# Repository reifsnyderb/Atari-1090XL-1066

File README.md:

# 1066

64k/256k 1090XL DRAM Card

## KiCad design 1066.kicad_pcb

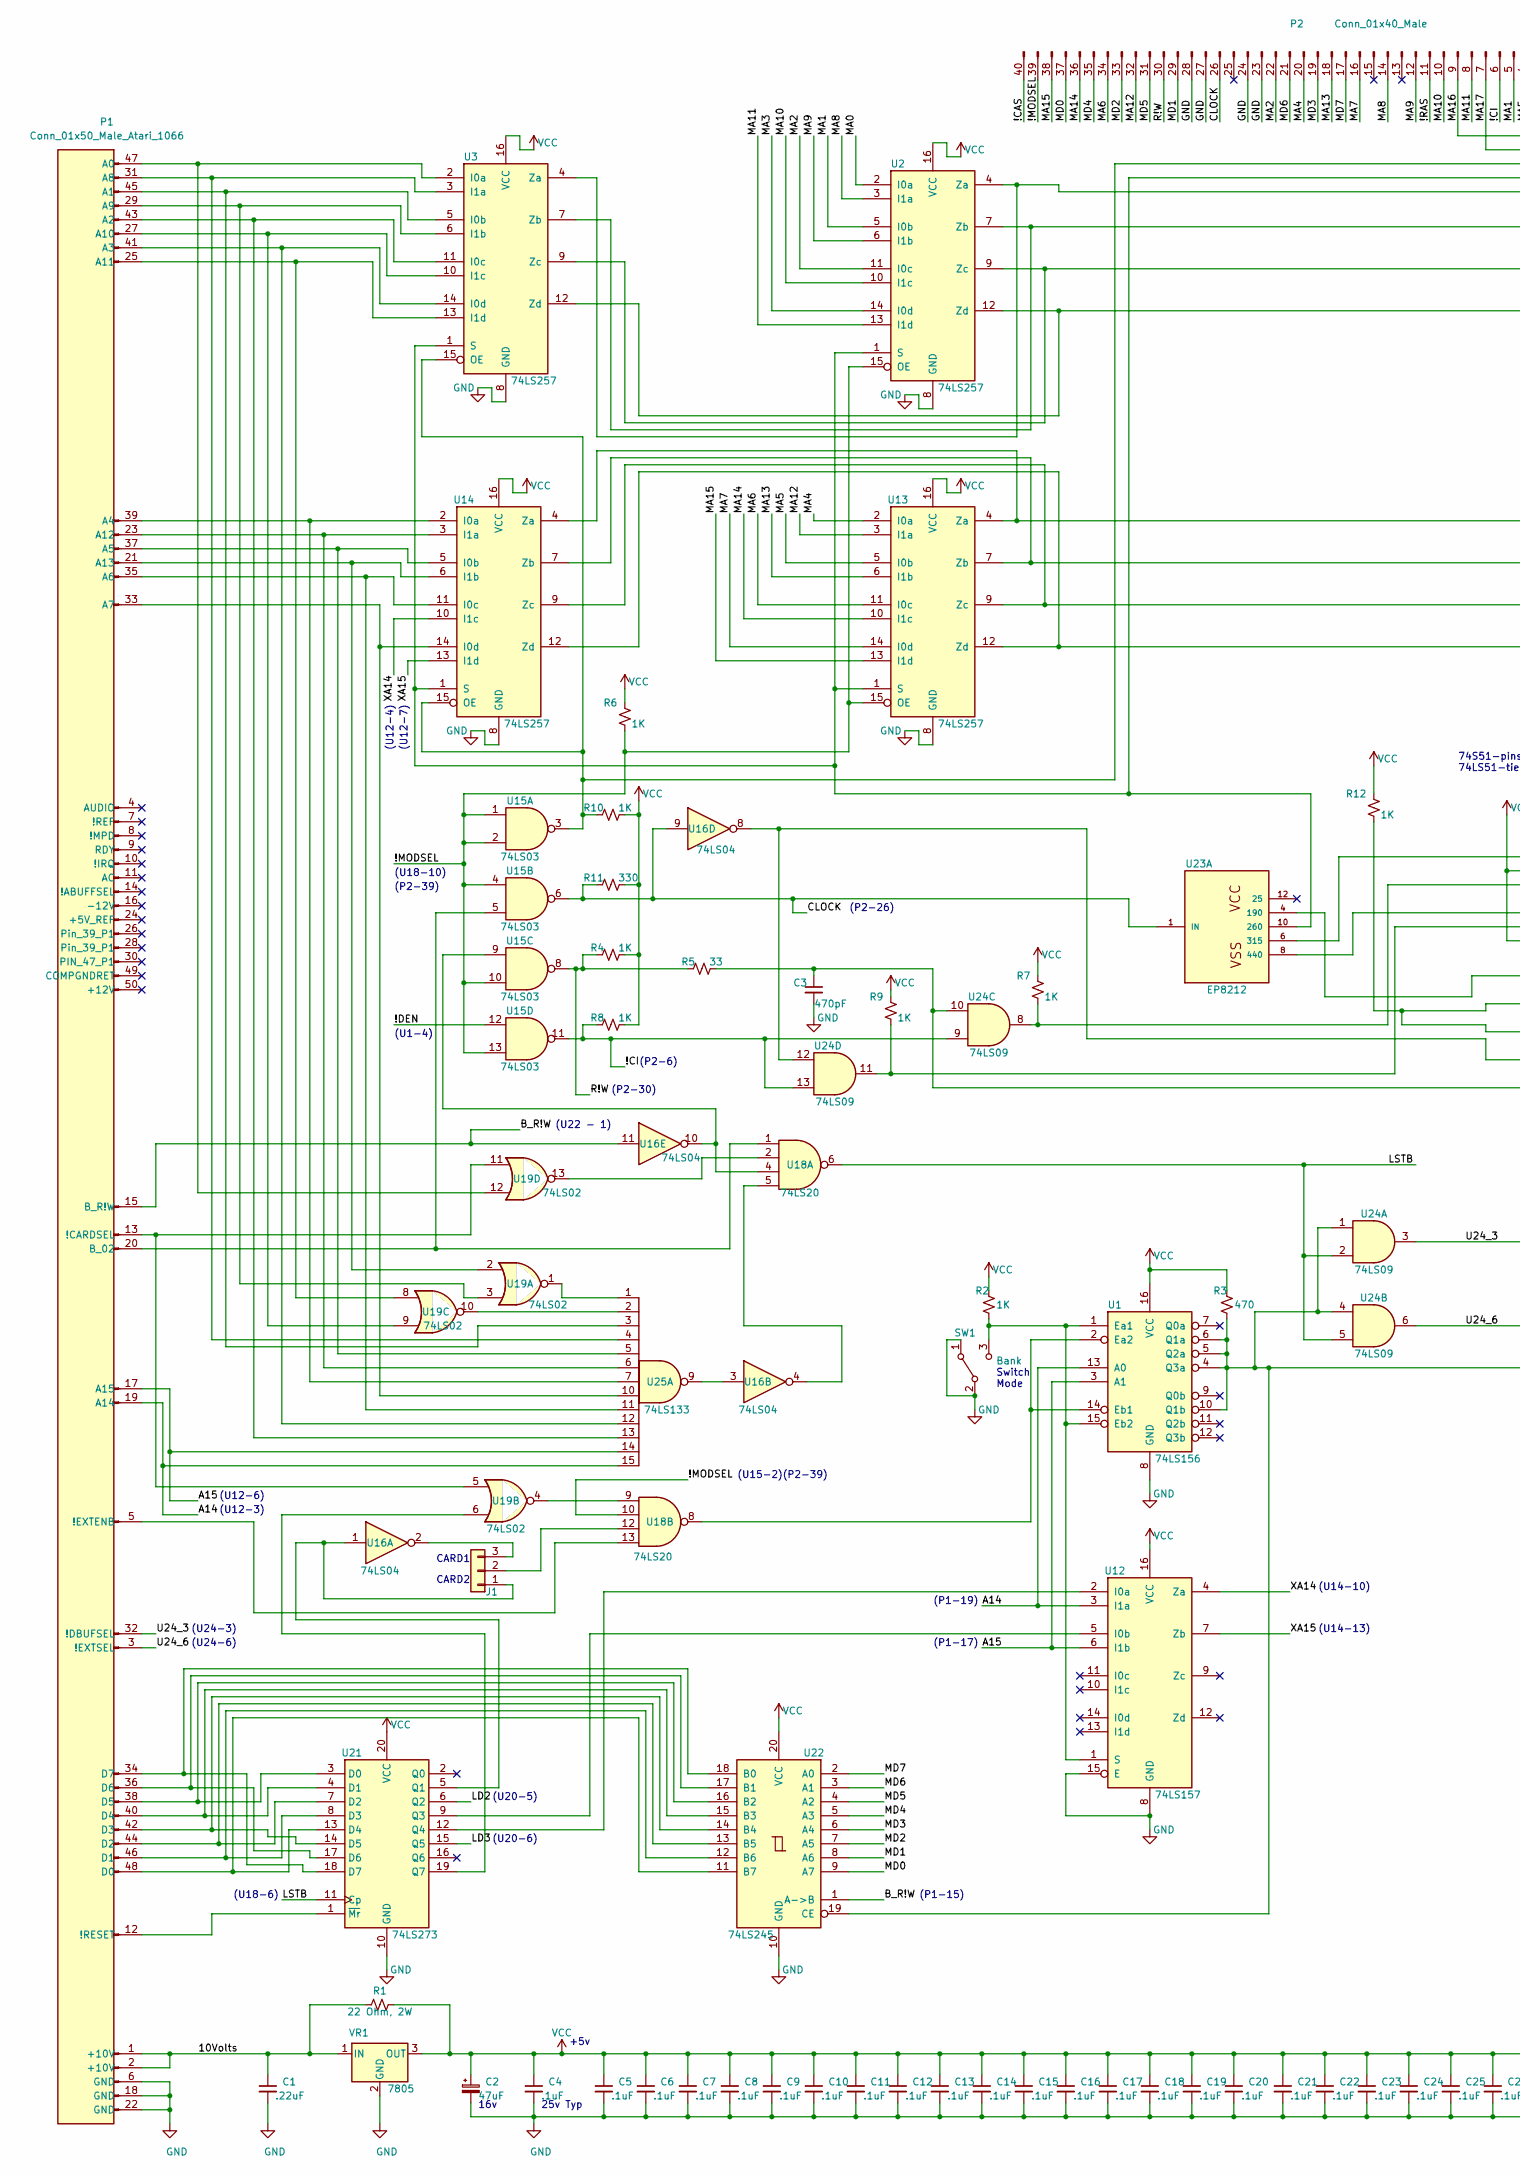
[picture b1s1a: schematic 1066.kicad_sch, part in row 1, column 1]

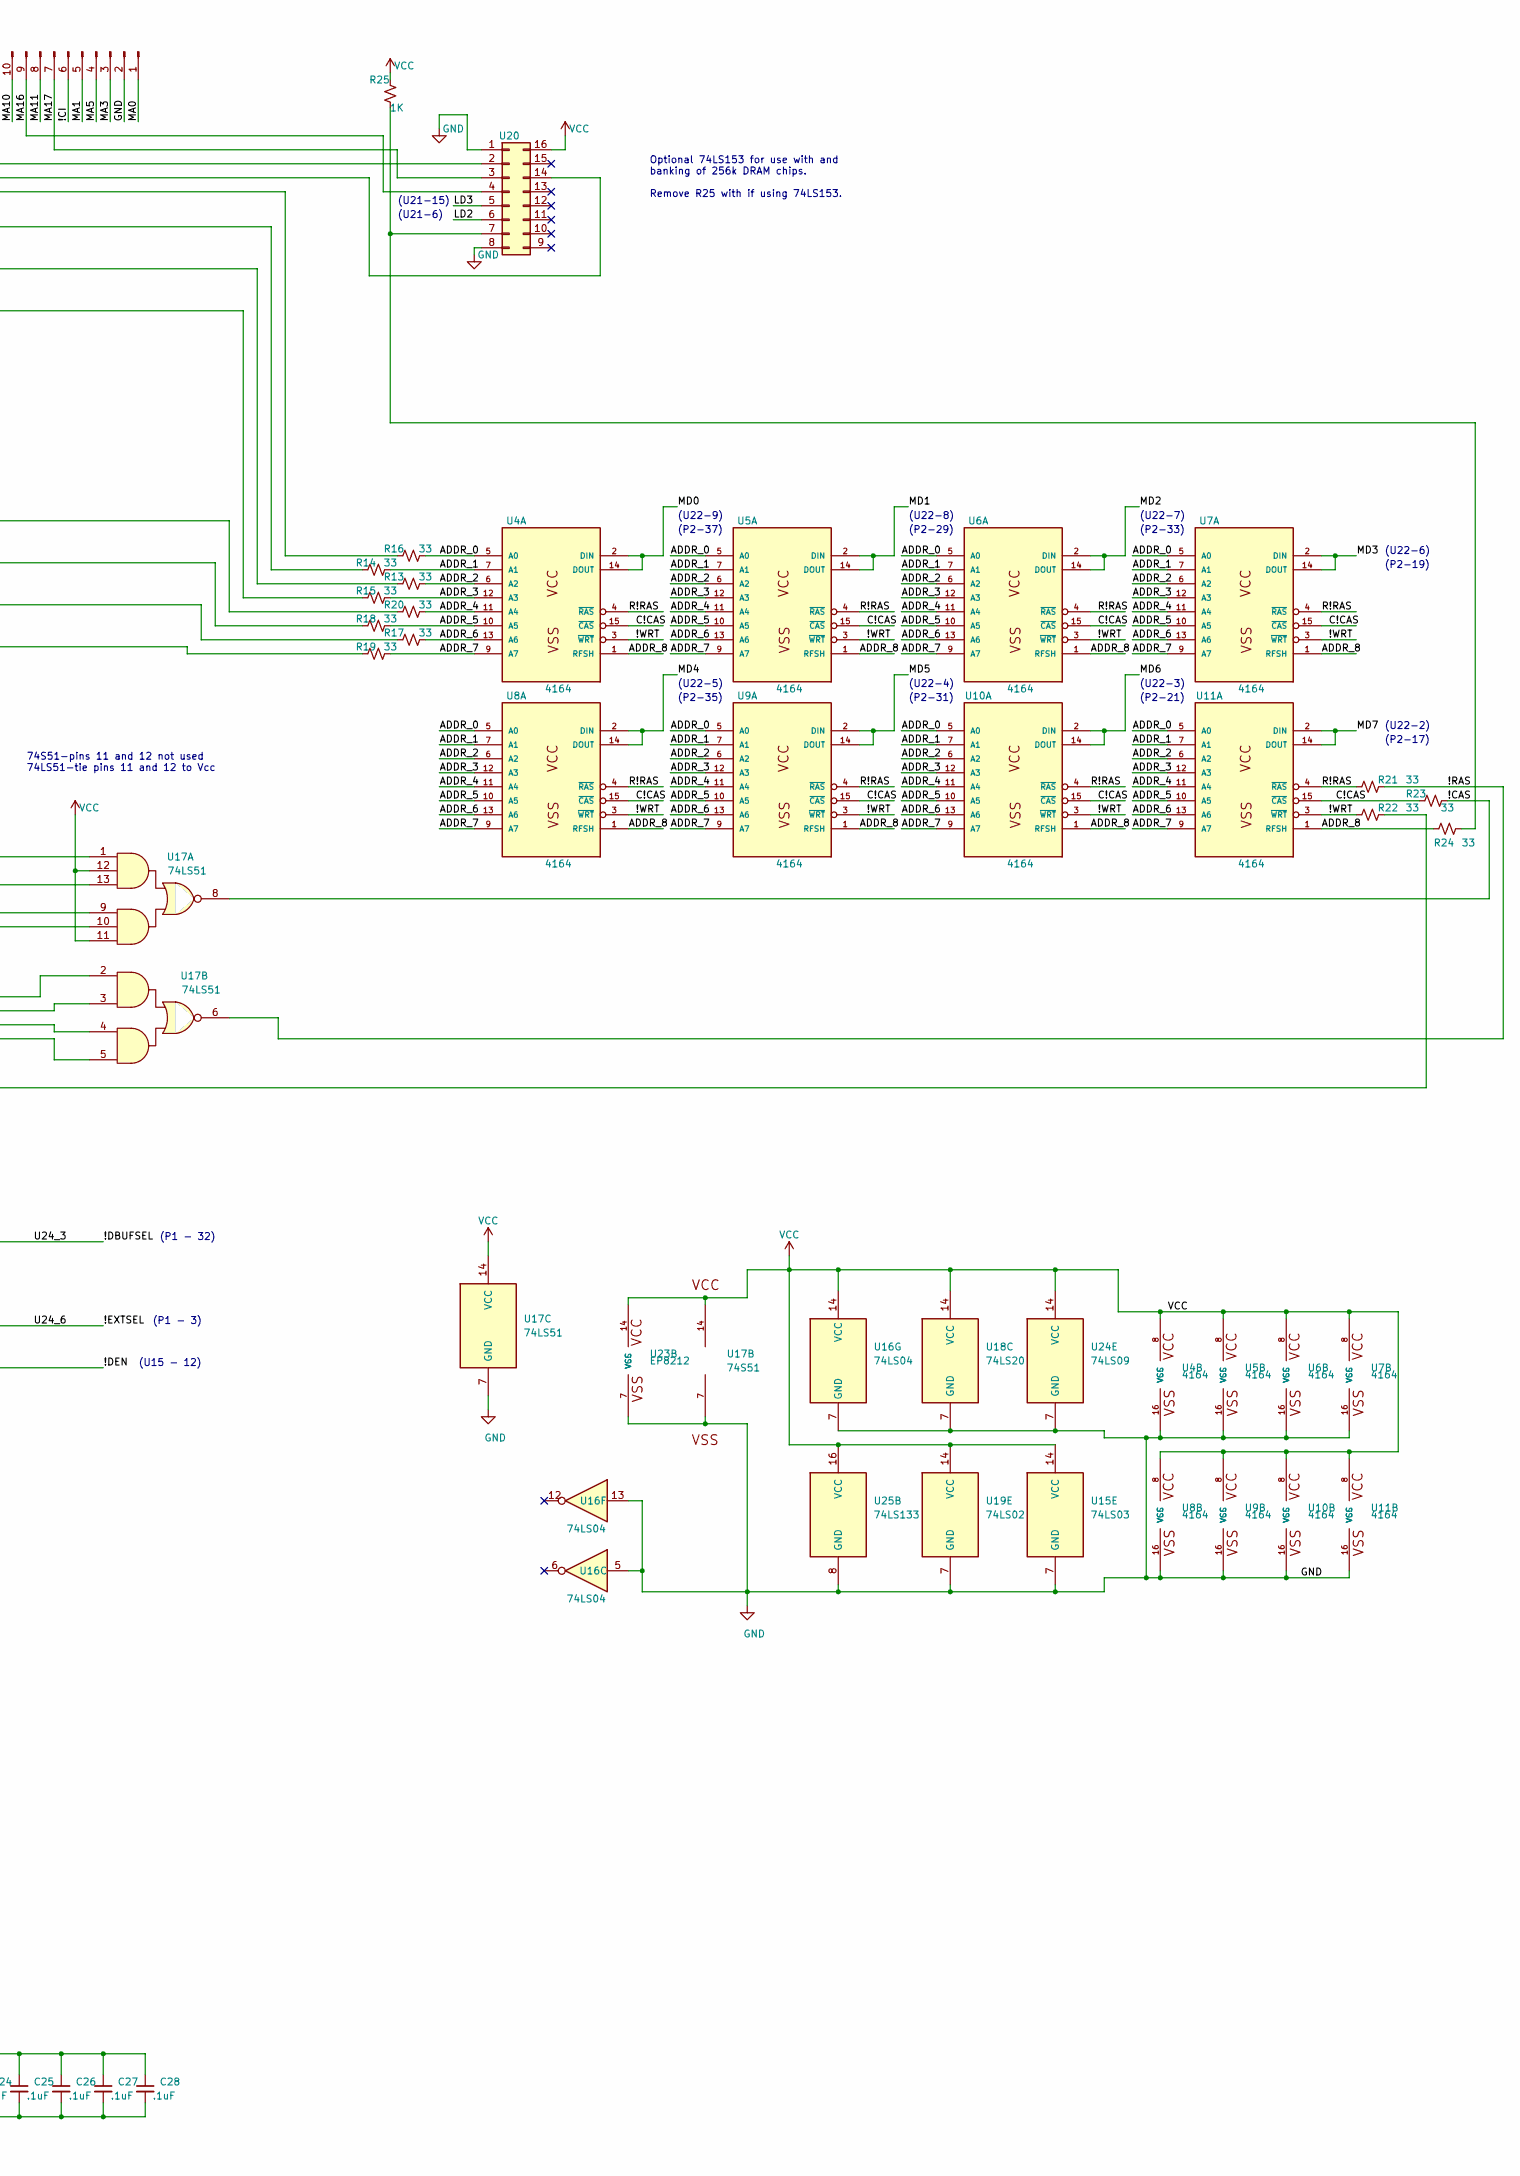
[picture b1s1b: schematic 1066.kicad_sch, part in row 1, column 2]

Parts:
C1: .22uF; C_Axial_L3.8mm_D2.6mm_P7.50mm_Horizontal
C2: 47uF; CP_Axial_L21.0mm_D8.0mm_P28.00mm_Horizontal
C3: 470pF; C_Rect_L24.0mm_W8.3mm_P22.50mm_MKT
C4, C5, C6, C7, C8, C9, C10, C11, C12, C13, C14, C15, C16, C17, C18, C19, C20, C21, C22, C23, C24, C25, C26, C27, C28: .1uF; C_Axial_L3.8mm_D2.6mm_P7.50mm_Horizontal
J1: Conn_01x03; PinHeader_1x03_P2.54mm_Vertical
P1: Conn_01x50_Male_Atari_1066; PARALLEL_BUS_INTERFACE_DEVICE
P2: Conn_01x40_Male; PinHeader_2x20_P2.54mm_Vertical
R1: 22 Ohm, 2W; R_Axial_DIN0516_L15.5mm_D5.0mm_P30.48mm_Horizontal
R2, R4, R6, R7, R8, R9, R10, R12, R25: 1K; R_Axial_DIN0207_L6.3mm_D2.5mm_P10.16mm_Horizontal
R3: 470; R_Axial_DIN0207_L6.3mm_D2.5mm_P10.16mm_Horizontal
R5, R13, R14, R15, R16, R17, R18, R19, R20, R21, R22, R23, R24: 33; R_Axial_DIN0207_L6.3mm_D2.5mm_P10.16mm_Horizontal
R11: 330; R_Axial_DIN0207_L6.3mm_D2.5mm_P10.16mm_Horizontal
SW1: Bank; SPDT_Switch
U1: 74LS156; DIP-16_W7.62mm_Socket
U2, U3, U13, U14: 74LS257; DIP-16_W7.62mm
U4, U5, U6, U7, U8, U9, U10, U11: 4164; DIP-16_W7.62mm
U12: 74LS157; DIP-16_W7.62mm
U15: 74LS03; DIP-14_W7.62mm
U16: 74LS04; DIP-14_W7.62mm
U17: 74S51; DIP-14_W7.62mm_Socket
U18: 74LS20; DIP-14_W7.62mm
U19: 74LS02; DIP-14_W7.62mm
U20: Conn_02x08_Counter_Clockwise; DIP-16_W7.62mm
U21: 74LS273; DIP-20_W7.62mm
U22: 74LS245; DIP-20_W7.62mm
U23: EP8212; DIP-14_W7.62mm
U24: 74LS09; DIP-14_W7.62mm
U25: 74LS133; DIP-16_W7.62mm
VR1: 7805; TO-220-3_Horizontal_TabDown

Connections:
/10Volts: C1.1, P1.1 (+10V), P1.2 (+10V), R1.2, VR1.1 (IN)
/!CAS: P2.40, R23.1, U17.8
/!CI: P2.6, R8.2, U15.11, U24.9, U24.13
/!DBUFSEL: P1.32 (!DBUFSEL), U24.3
/!DEN: R3.2, U1.4 (Q3a), U1.5 (Q2a), U1.6 (Q1a), U1.10 (Q1b), U15.12, U22.19 (CE), U24.1, U24.4
/!EXTSEL: P1.3 (!EXTSEL), U24.6
/!MODSEL: P2.39, R6.1, U2.15 (OE), U13.15 (OE), U15.1, U15.2, U15.4, U15.10, U15.13, U18.10
/!RAS: P2.11, R21.1, U17.6
/!WRT: R22.2, U4.3 (~WRT), U5.3 (~WRT), U6.3 (~WRT), U7.3 (~WRT), U8.3 (~WRT), U9.3 (~WRT), U10.3 (~WRT), U11.3 (~WRT)
/A14: P1.19 (A14), U1.13 (A0), U12.3 (I1a), U25.15
/A15: P1.17 (A15), U1.3 (A1), U12.6 (I1b), U25.14
/ADDR_0: R16.1, U4.5 (A0), U5.5 (A0), U6.5 (A0), U7.5 (A0), U8.5 (A0), U9.5 (A0), U10.5 (A0), U11.5 (A0)
/ADDR_1: R14.1, U4.7 (A1), U5.7 (A1), U6.7 (A1), U7.7 (A1), U8.7 (A1), U9.7 (A1), U10.7 (A1), U11.7 (A1)
/ADDR_2: R13.1, U4.6 (A2), U5.6 (A2), U6.6 (A2), U7.6 (A2), U8.6 (A2), U9.6 (A2), U10.6 (A2), U11.6 (A2)
/ADDR_3: R15.1, U4.12 (A3), U5.12 (A3), U6.12 (A3), U7.12 (A3), U8.12 (A3), U9.12 (A3), U10.12 (A3), U11.12 (A3)
/ADDR_4: R20.1, U4.11 (A4), U5.11 (A4), U6.11 (A4), U7.11 (A4), U8.11 (A4), U9.11 (A4), U10.11 (A4), U11.11 (A4)
/ADDR_5: R18.1, U4.10 (A5), U5.10 (A5), U6.10 (A5), U7.10 (A5), U8.10 (A5), U9.10 (A5), U10.10 (A5), U11.10 (A5)
/ADDR_6: R17.1, U4.13 (A6), U5.13 (A6), U6.13 (A6), U7.13 (A6), U8.13 (A6), U9.13 (A6), U10.13 (A6), U11.13 (A6)
/ADDR_7: R19.1, U4.9 (A7), U5.9 (A7), U6.9 (A7), U7.9 (A7), U8.9 (A7), U9.9 (A7), U10.9 (A7), U11.9 (A7)
/ADDR_8: R24.2, U4.1 (RFSH), U5.1 (RFSH), U6.1 (RFSH), U7.1 (RFSH), U8.1 (RFSH), U9.1 (RFSH), U10.1 (RFSH), U11.1 (RFSH)
/B_R!W: P1.15 (B_R!W), U16.11, U22.1 (A->B)
/C!CAS: R23.2, U4.15 (~CAS), U5.15 (~CAS), U6.15 (~CAS), U7.15 (~CAS), U8.15 (~CAS), U9.15 (~CAS), U10.15 (~CAS), U11.15 (~CAS)
/CLOCK: P2.26, R11.2, U15.6, U16.9, U23.1 (IN)
/LD2: U20.6, U21.6 (Q2)
/LD3: U20.5, U21.15 (Q5)
/LSTB: U18.6, U21.11 (Cp), U24.2, U24.5
/MA0: P2.1, U2.2 (I0a)
/MA1: P2.5, U2.5 (I0b)
/MA2: P2.22, U2.11 (I0c)
/MA3: P2.3, U2.14 (I0d)
/MA4: P2.20, U13.2 (I0a)
/MA5: P2.4, U13.5 (I0b)
/MA6: P2.34, U13.11 (I0c)
/MA7: P2.16, U13.14 (I0d)
/MA8: P2.14, U2.3 (I1a)
/MA9: P2.12, U2.6 (I1b)
/MA10: P2.10, U2.10 (I1c)
/MA11: P2.8, U2.13 (I1d)
/MA12: P2.32, U13.3 (I1a)
/MA13: P2.18, U13.6 (I1b)
/MA14: P2.36, U13.10 (I1c)
/MA15: P2.38, U13.13 (I1d)
/MA16: P2.9, U20.4
/MA17: P2.7, U20.3
/MD0: P2.37, U4.2 (DIN), U4.14 (DOUT), U22.9 (A7)
/MD1: P2.29, U5.2 (DIN), U5.14 (DOUT), U22.8 (A6)
/MD2: P2.33, U6.2 (DIN), U6.14 (DOUT), U22.7 (A5)
/MD3: P2.19, U7.2 (DIN), U7.14 (DOUT), U22.6 (A4)
/MD4: P2.35, U8.2 (DIN), U8.14 (DOUT), U22.5 (A3)
/MD5: P2.31, U9.2 (DIN), U9.14 (DOUT), U22.4 (A2)
/MD6: P2.21, U10.2 (DIN), U10.14 (DOUT), U22.3 (A1)
/MD7: P2.17, U11.2 (DIN), U11.14 (DOUT), U22.2 (A0)
/R!RAS: R21.2, U4.4 (~RAS), U5.4 (~RAS), U6.4 (~RAS), U7.4 (~RAS), U8.4 (~RAS), U9.4 (~RAS), U10.4 (~RAS), U11.4 (~RAS)
/R!W: P2.30, R4.2, R5.2, U15.8
/XA14: U12.4 (Za), U14.10 (I1c)
/XA15: U12.7 (Zb), U14.13 (I1d)
GND: C1.2, C2.2, C3.2, C4.2, C5.2, C6.2, C7.2, C8.2, C9.2, C10.2, C11.2, C12.2, C13.2, C14.2, C15.2, C16.2, C17.2, C18.2, C19.2, C20.2, C21.2, C22.2, C23.2, C24.2, C25.2, C26.2, C27.2, C28.2, P1.6 (GND), P1.18 (GND), P1.22 (GND), P2.2, P2.23, P2.24, P2.27, P2.28, SW1.1 (A), SW1.2 (B), U1.8 (GND), U2.8 (GND), U3.8 (GND), U4.16 (VSS), U5.16 (VSS), U6.16 (VSS), U7.16 (VSS), U8.16 (VSS), U9.16 (VSS), U10.16 (VSS), U11.16 (VSS), U12.8 (GND), U12.15 (E), U13.8 (GND), U14.8 (GND), U15.7 (GND), U16.5, U16.7 (GND), U16.13, U17.7 (GND), U18.7 (GND), U19.7 (GND), U20.1, U20.8, U21.10 (GND), U22.10 (GND), U23.7 (VSS), U24.7 (GND), U25.8 (GND), VR1.2 (GND)
unnamed: C3.1, R5.1, R22.1, U24.10
unnamed: J1.1, U16.1, U21.5 (Q1)
unnamed: J1.2, U18.12
unnamed: J1.3, U16.2
unnamed: P1.5 (!EXTENB), U18.13
unnamed: P1.12 (!RESET), U21.1 (~Mr)
unnamed: P1.13 (!CARDSEL), U19.5, U19.11
unnamed: P1.20 (B_02), U15.5, U18.1
unnamed: P1.21 (A13), U14.6 (I1b), U19.2
unnamed: P1.23 (A12), U14.3 (I1a), U25.6
unnamed: P1.25 (A11), U3.13 (I1d), U19.8
unnamed: P1.27 (A10), U3.10 (I1c), U19.9
unnamed: P1.29 (A9), U3.6 (I1b), U19.3
unnamed: P1.31 (A8), U3.3 (I1a), U25.4
unnamed: P1.33 (A7), U14.14 (I0d), U25.10
unnamed: P1.34 (D7), U21.18 (D7), U22.18 (B0)
unnamed: P1.35 (A6), U14.11 (I0c), U25.11
unnamed: P1.36 (D6), U21.17 (D6), U22.17 (B1)
unnamed: P1.37 (A5), U14.5 (I0b), U25.5
unnamed: P1.38 (D5), U21.3 (D0), U22.16 (B2)
unnamed: P1.39 (A4), U14.2 (I0a), U25.7
unnamed: P1.40 (D4), U21.4 (D1), U22.15 (B3)
unnamed: P1.41 (A3), U3.14 (I0d), U25.12
unnamed: P1.42 (D3), U21.14 (D5), U22.14 (B4)
unnamed: P1.43 (A2), U3.11 (I0c), U25.13
unnamed: P1.44 (D2), U21.7 (D2), U22.13 (B5)
unnamed: P1.45 (A1), U3.5 (I0b), U25.3
unnamed: P1.46 (D1), U21.8 (D3), U22.12 (B6)
unnamed: P1.47 (A0), U3.2 (I0a), U19.12
unnamed: P1.48 (D0), U21.13 (D4), U22.11 (B7)
unnamed: R2.2, SW1.3 (C), U1.1 (Ea1), U1.15 (Eb2), U12.1 (S)
unnamed: R7.1, U17.13, U24.8
unnamed: R9.1, U17.10, U24.11
unnamed: R10.2, U3.15 (OE), U14.15 (OE), U15.3, U20.2
unnamed: R12.1, U17.3, U17.4
unnamed: R13.2, U2.9 (Zc), U3.9 (Zc)
unnamed: R14.2, U2.7 (Zb), U3.7 (Zb)
unnamed: R15.2, U2.12 (Zd), U3.12 (Zd)
unnamed: R16.2, U2.4 (Za), U3.4 (Za)
unnamed: R17.2, U13.9 (Zc), U14.9 (Zc)
unnamed: R18.2, U13.7 (Zb), U14.7 (Zb)
unnamed: R19.2, U13.12 (Zd), U14.12 (Zd)
unnamed: R20.2, U13.4 (Za), U14.4 (Za)
unnamed: R24.1, R25.1, U20.7
unnamed: U1.2 (Ea2), U1.14 (Eb1), U18.8
unnamed: U12.2 (I0a), U21.12 (Q4)
unnamed: U12.5 (I0b), U21.9 (Q3)
unnamed: U2.1 (S), U3.1 (S), U13.1 (S), U14.1 (S), U20.14, U23.10 (260)
unnamed: U15.9, U16.10, U18.4
unnamed: U16.3, U25.9
unnamed: U16.4, U18.5
unnamed: U16.8, U17.5, U24.12
unnamed: U17.1, U23.6 (315)
unnamed: U17.2, U23.4 (190)
unnamed: U17.9, U23.8 (440)
unnamed: U18.2, U19.13
unnamed: U18.9, U19.4
unnamed: U19.1, U25.1
unnamed: U19.6, U21.19 (Q7)
unnamed: U19.10, U25.2
VCC: C2.1, C4.1, C5.1, C6.1, C7.1, C8.1, C9.1, C10.1, C11.1, C12.1, C13.1, C14.1, C15.1, C16.1, C17.1, C18.1, C19.1, C20.1, C21.1, C22.1, C23.1, C24.1, C25.1, C26.1, C27.1, C28.1, R1.1, R2.1, R3.1, R4.1, R6.2, R7.2, R8.1, R9.2, R10.1, R11.1, R12.2, R25.2, U1.16 (VCC), U2.16 (VCC), U3.16 (VCC), U4.8 (VCC), U5.8 (VCC), U6.8 (VCC), U7.8 (VCC), U8.8 (VCC), U9.8 (VCC), U10.8 (VCC), U11.8 (VCC), U12.16 (VCC), U13.16 (VCC), U14.16 (VCC), U15.14 (VCC), U16.14 (VCC), U17.11, U17.12, U17.14 (VCC), U18.14 (VCC), U19.14 (VCC), U20.16, U21.20 (VCC), U22.20 (VCC), U23.14 (VCC), U24.14 (VCC), U25.16 (VCC), VR1.3 (OUT)

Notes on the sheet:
(P2-19)
(U22-5)
CARD1
(U14-10)
(P2-30)
(P1-19)
(U22-2)
(U14-13)
(U22-3)
(P2-37)
(P1 - 3)
(U12-6)
(U18-6)
(U22-9)
(P2-33)
(U12-3)
(P1-15)
+5v
(P2-6)
(U12-4)
(U24-6)
(U21-15)
(U20-6)
(P2-29)
25v Typ
(U24-3)
(U15 - 12)
(P1-17)
(U21-6)
(U20-5)
(U1-4)
(P2-31)
(P2-26)
(U12-7)
Optional 74LS153 for use with and banking of 256k DRAM chips. Remove R25 with if using 74LS153.
74S51-pins 11 and 12 not used 74LS51-tie pins 11 and 12 to Vcc
Switch Mode
(U22-8)
(U18-10)
(U22-4)

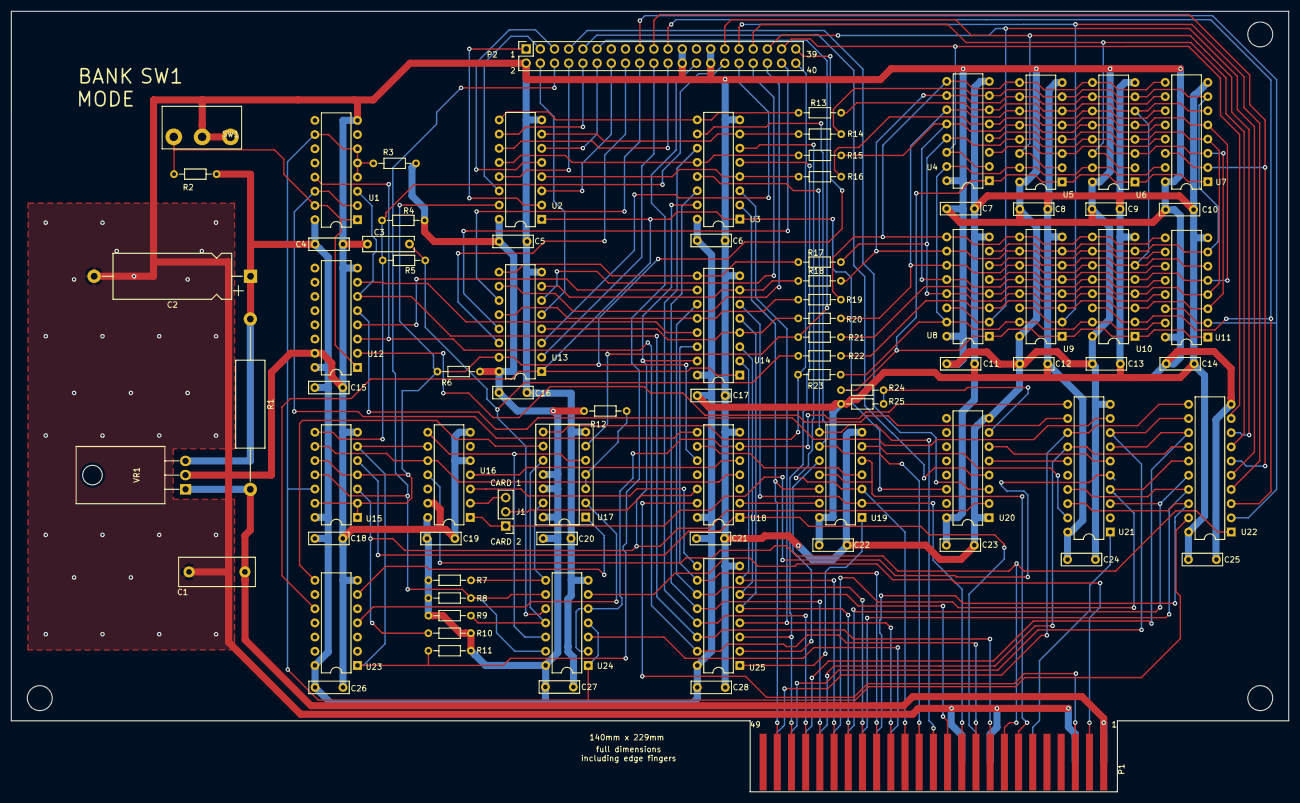
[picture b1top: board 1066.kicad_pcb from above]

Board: 2 copper layers, 228.6 x 139.7 mm, 83 parts (1 on the bottom side), 118 nets.
